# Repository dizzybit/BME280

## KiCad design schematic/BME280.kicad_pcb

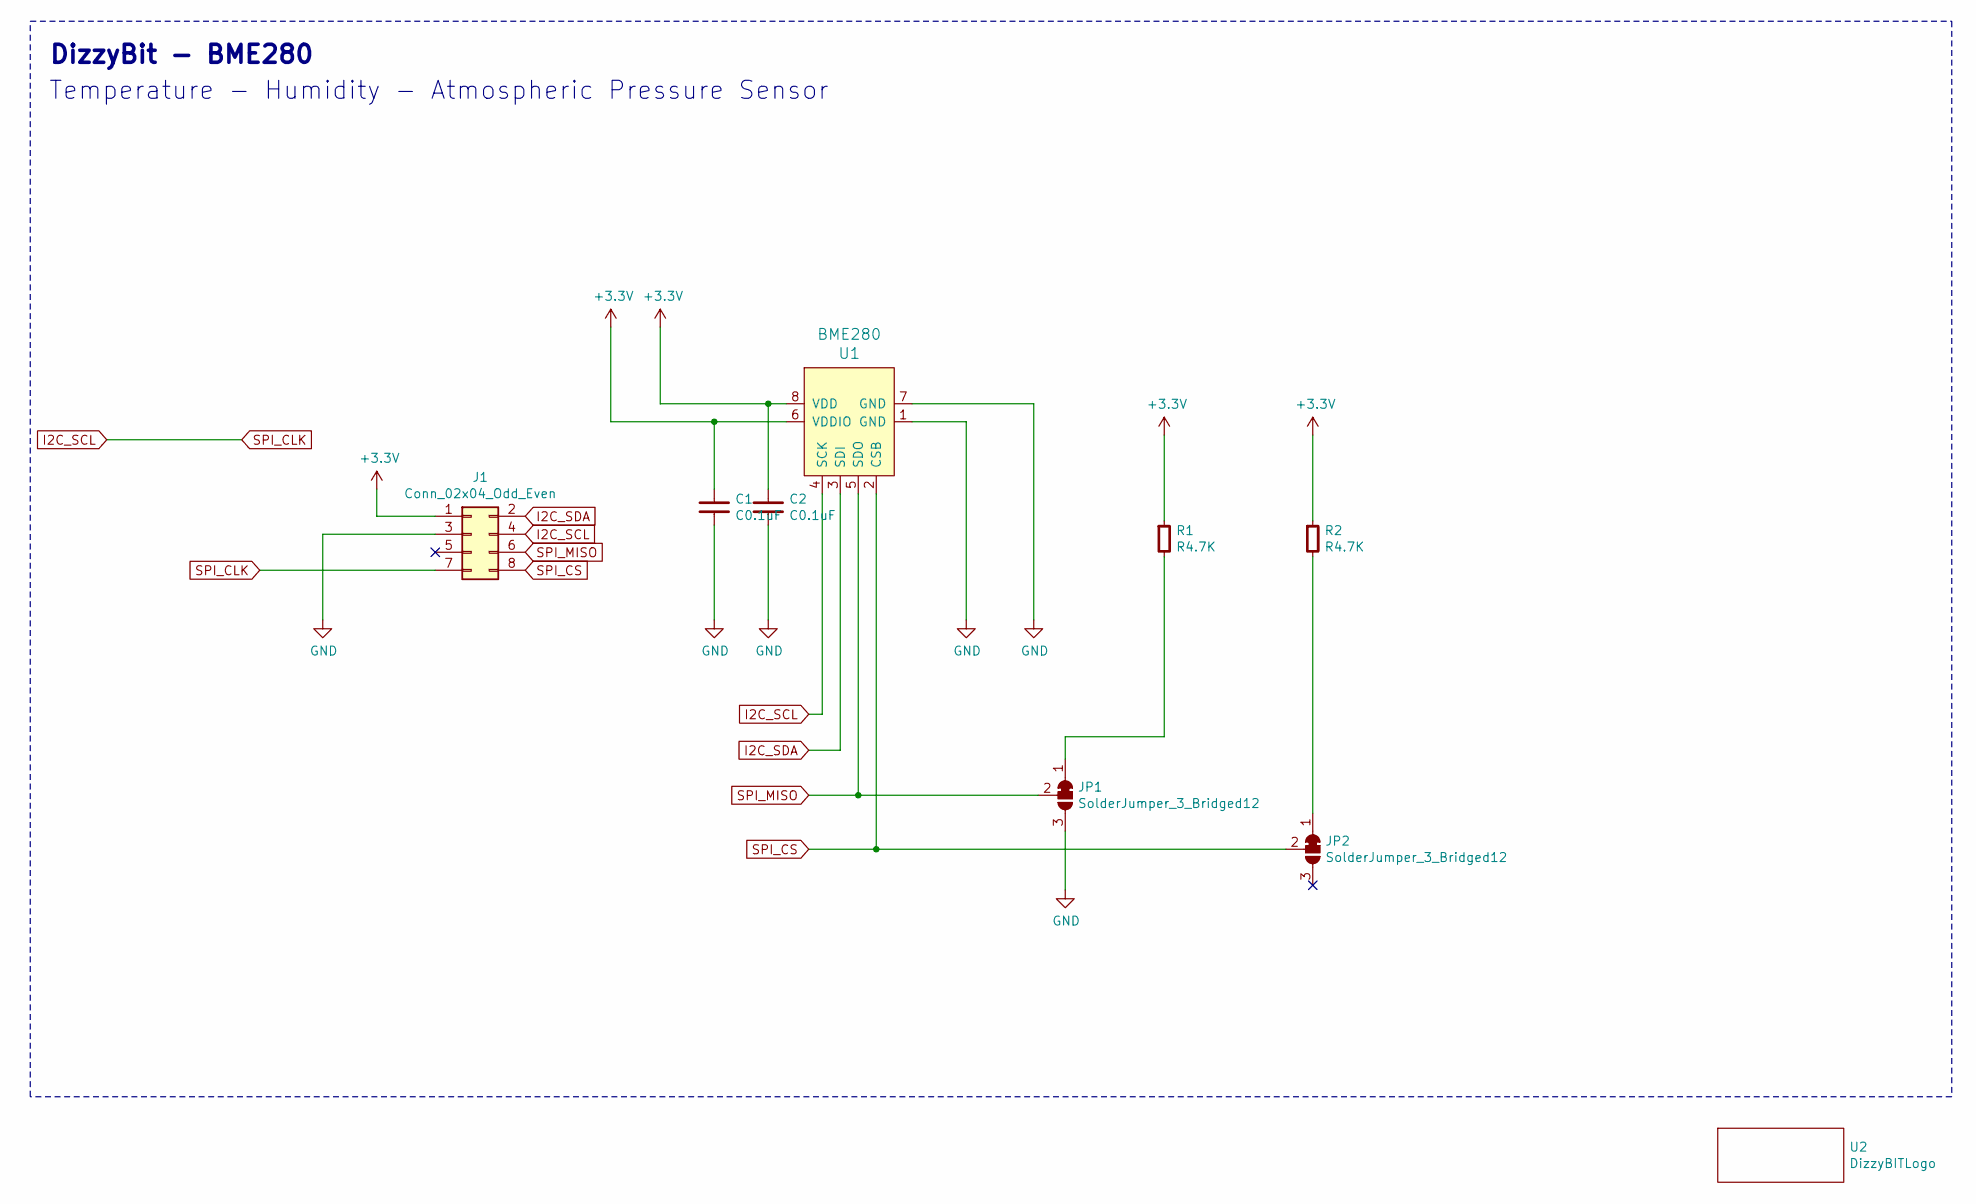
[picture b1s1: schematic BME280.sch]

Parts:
C1, C2: C0.1uF; C_0603_1608Metric
J1: Conn_02x04_Odd_Even; PinSocket_2x04_P2.00mm_Vertical
JP1, JP2: SolderJumper_3_Bridged12; DizzyBit-SolderJumper-3-Open
R1, R2: R4.7K; R_0603_1608Metric
U1: BME280; Pressure_Sensor_LGA-8_2.5x2.5mm_BME280; MPN BME280; Digi-Key_PN 828-1063-1-ND
U2: DizzyBITLogo; DizzyBIT_silk_6.4

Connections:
+3V3: C1.1, C2.1, J1.1, R1.1, R2.1, U1.6 (VDDIO), U1.8 (VDD)
GND: C1.2, C2.2, J1.3, JP1.3 (B), U1.1 (GND), U1.7 (GND)
I2C_SCL: J1.4, J1.7, U1.4 (SCK)
I2C_SDA: J1.2, U1.3 (SDI)
unnamed: JP1.1 (A), R1.2
unnamed: JP2.1 (A), R2.2
SPI_CS: J1.8, JP2.2 (C), U1.2 (CSB)
SPI_MISO: J1.6, JP1.2 (C), U1.5 (SDO)

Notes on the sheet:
DizzyBit - BME280
Temperature - Humidity - Atmospheric‎ Pressure Sensor

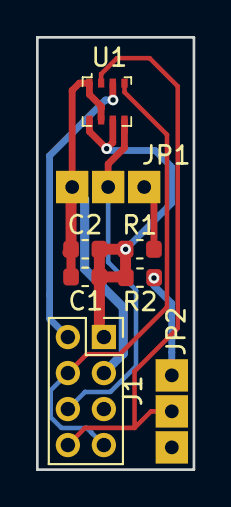
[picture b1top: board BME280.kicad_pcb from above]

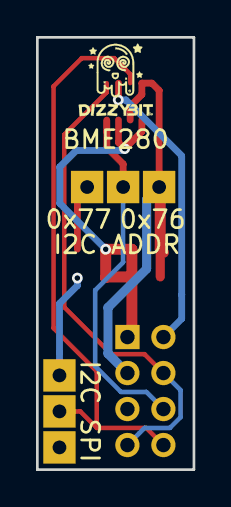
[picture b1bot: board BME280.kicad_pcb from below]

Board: 2 copper layers, 8.7 x 24.0 mm, 9 parts (2 on the bottom side), 8 nets.

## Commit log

2019-09-27 BME280 schematic
2019-10-02 Changed pin numbers
2019-10-04 Added 3D and Gerber files
